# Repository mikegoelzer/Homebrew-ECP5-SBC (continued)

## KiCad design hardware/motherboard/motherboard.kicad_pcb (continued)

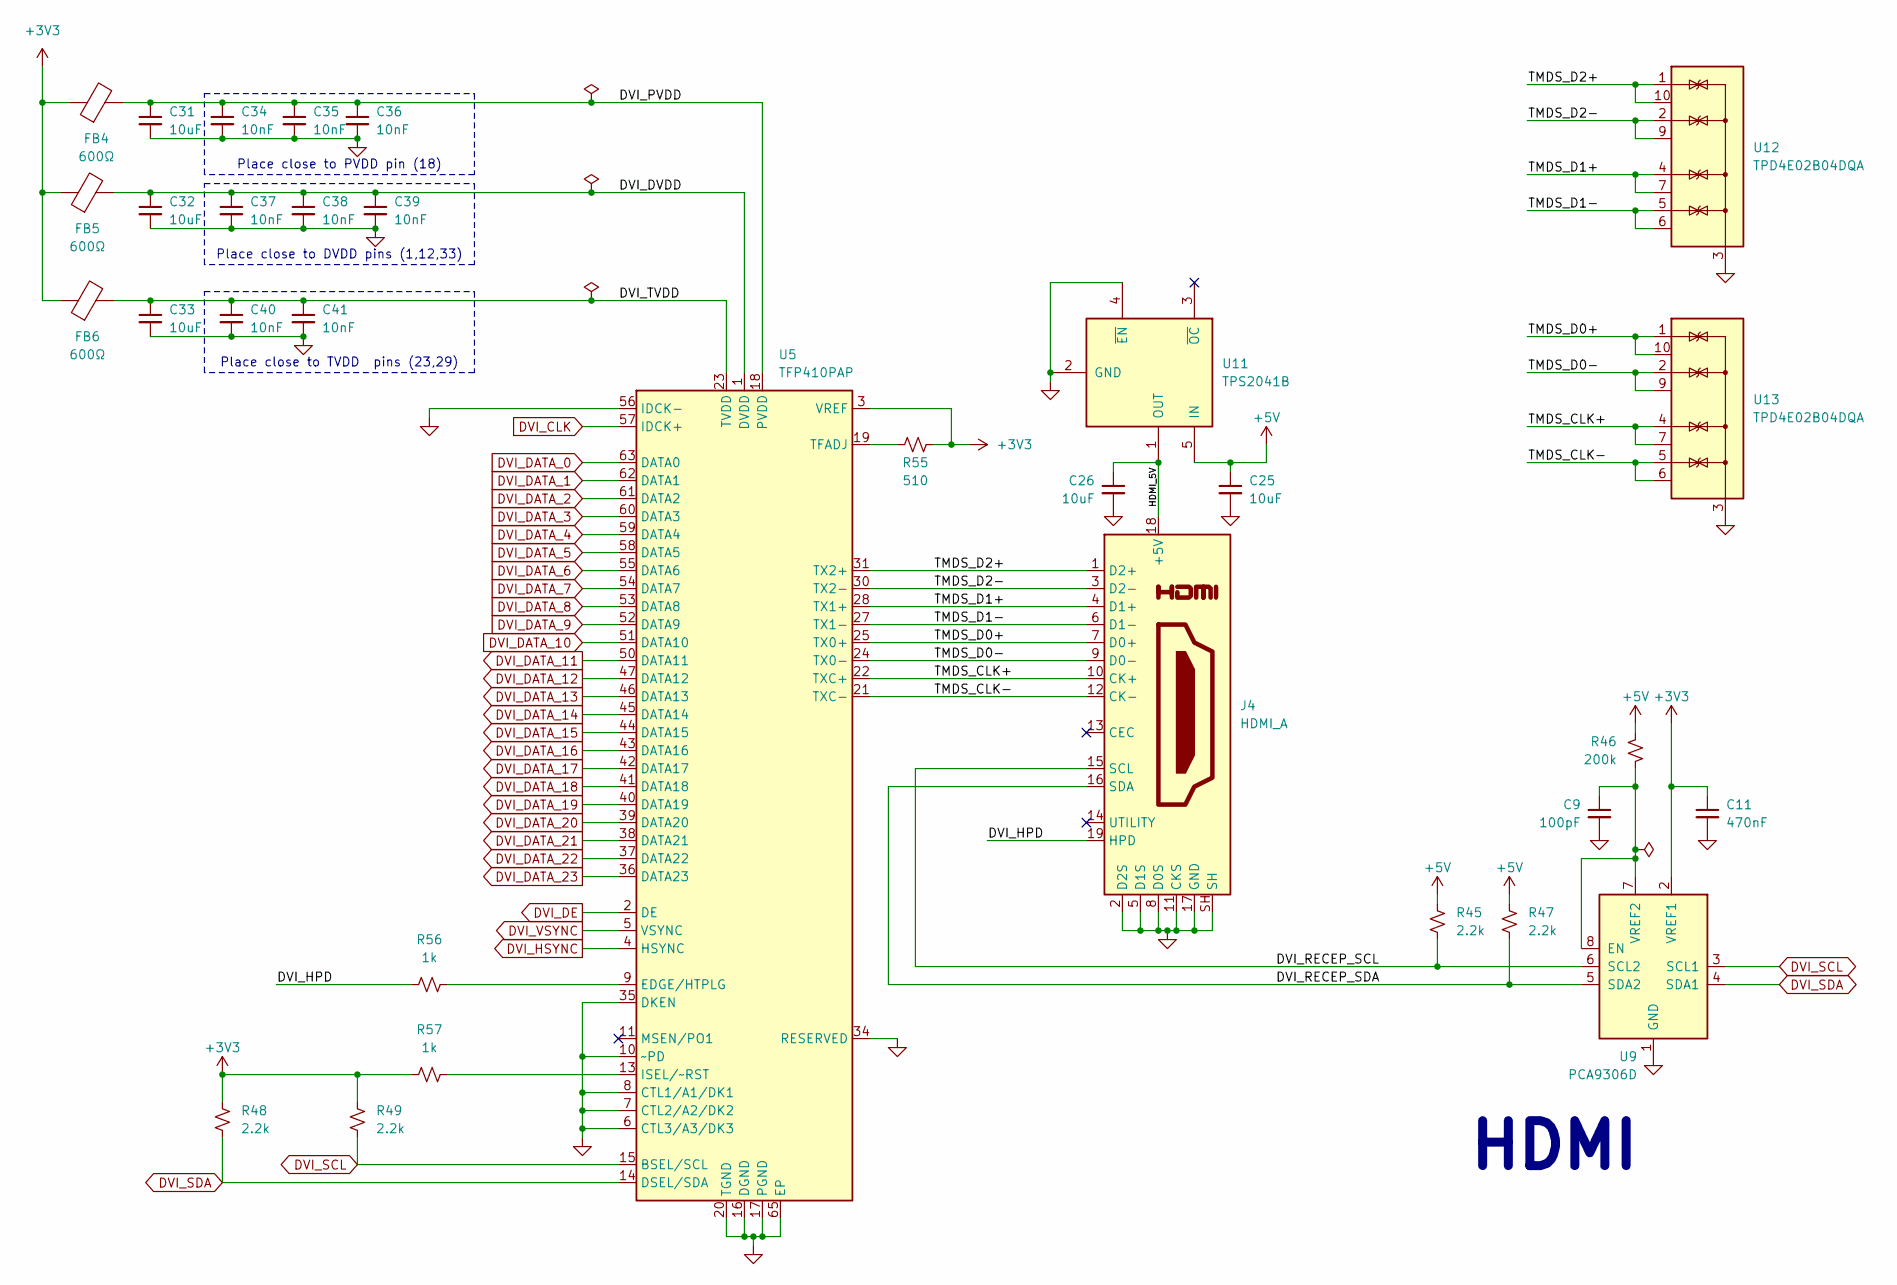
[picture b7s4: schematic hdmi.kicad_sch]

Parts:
C9: 100pF; C_0805_2012Metric_Pad1.18x1.45mm_HandSolder; MPN CC0805KRX7R9BB101
C11: 470nF; C_0805_2012Metric_Pad1.18x1.45mm_HandSolder; MPN CC0805KKX7R8BB474
C25, C26, C31, C32, C33: 10uF; C_0805_2012Metric_Pad1.18x1.45mm_HandSolder; MPN CC0805KKX5R8BB106
C34, C35, C36, C37, C38, C39, C40, C41: 10nF; C_0805_2012Metric_Pad1.18x1.45mm_HandSolder; MPN CC0805KRX7R9BB103
FB4, FB5, FB6: 600Ω; L_0603_1608Metric_Pad1.05x0.95mm_HandSolder; MPN BLM18RK601SN1D
J4: HDMI_A; HDMI_A_Molex_208658-1001_Horizontal; MPN 2086581001
R45, R47, R48, R49: 2.2k; R_0805_2012Metric_Pad1.15x1.40mm_HandSolder; MPN RC0805FR-072K2L
R46: 200k; R_0805_2012Metric_Pad1.15x1.40mm_HandSolder; MPN RC0805FR-07200KL
R55: 510; R_0805_2012Metric_Pad1.15x1.40mm_HandSolder; MPN RC0805FR-07510RL
R56, R57: 1k; R_0805_2012Metric_Pad1.15x1.40mm_HandSolder; MPN RC0805FR-071KL
U5: TFP410PAP; HTQFP-64-1EP_10x10mm_P0.5mm_EP8x8mm_Mask4.4x4.4mm_ThermalVi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; MPN TFP410PAP
U9: PCA9306D; SO-8_3.9x4.9mm_P1.27mm; MPN PCA9306D,118
U11: TPS2041B; SOT-23-5; MPN TPS2041BDBVR
U12, U13: TPD4E02B04DQA; USON-10_2.5x1.0mm_P0.5mm; MPN TPD4E02B04DQAR

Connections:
+3V3: C11.1, FB4.1, FB5.1, FB6.1, R48.1, R49.1, R55.2, R57.1, U5.3 (VREF), U9.2 (VREF1); also elsewhere on the board
+5V: C25.1, R45.1, R46.1, R47.1, U11.5 (IN); also elsewhere on the board
/HDMI/DVI_DVDD: C32.1, C37.1, C38.1, C39.1, FB5.2, U5.1 (DVDD), U5.12 (DVDD), U5.33 (DVDD)
/HDMI/DVI_HPD: J4.19 (HPD), R56.1
/HDMI/DVI_PVDD: C31.1, C34.1, C35.1, C36.1, FB4.2, U5.18 (PVDD)
/HDMI/DVI_RECEP_SCL: J4.15 (SCL), R45.2, U9.6 (SCL2)
/HDMI/DVI_RECEP_SDA: J4.16 (SDA), R47.2, U9.5 (SDA2)
/HDMI/DVI_TVDD: C33.1, C40.1, C41.1, FB6.2, U5.23 (TVDD), U5.29 (TVDD)
/HDMI/HDMI_5V: C26.1, J4.18 (+5V), U11.1 (OUT)
/HDMI/TMDS_CLK+: J4.10 (CK+), U5.22 (TXC+), U13.4 (IO3), U13.7 (NC)
/HDMI/TMDS_CLK-: J4.12 (CK-), U5.21 (TXC-), U13.5 (IO4), U13.6 (NC)
/HDMI/TMDS_D0+: J4.7 (D0+), U5.25 (TX0+), U13.1 (IO1), U13.10 (NC)
/HDMI/TMDS_D0-: J4.9 (D0-), U5.24 (TX0-), U13.2 (IO2), U13.9 (NC)
/HDMI/TMDS_D1+: J4.4 (D1+), U5.28 (TX1+), U12.4 (IO3), U12.7 (NC)
/HDMI/TMDS_D1-: J4.6 (D1-), U5.27 (TX1-), U12.5 (IO4), U12.6 (NC)
/HDMI/TMDS_D2+: J4.1 (D2+), U5.31 (TX2+), U12.1 (IO1), U12.10 (NC)
/HDMI/TMDS_D2-: J4.3 (D2-), U5.30 (TX2-), U12.2 (IO2), U12.9 (NC)
DVI_CLK: U5.57 (IDCK+); also elsewhere on the board
DVI_DATA_0: U5.63 (DATA0); also elsewhere on the board
DVI_DATA_1: U5.62 (DATA1); also elsewhere on the board
DVI_DATA_2: U5.61 (DATA2); also elsewhere on the board
DVI_DATA_3: U5.60 (DATA3); also elsewhere on the board
DVI_DATA_4: U5.59 (DATA4); also elsewhere on the board
DVI_DATA_5: U5.58 (DATA5); also elsewhere on the board
DVI_DATA_6: U5.55 (DATA6); also elsewhere on the board
DVI_DATA_7: U5.54 (DATA7); also elsewhere on the board
DVI_DATA_8: U5.53 (DATA8); also elsewhere on the board
DVI_DATA_9: U5.52 (DATA9); also elsewhere on the board
DVI_DATA_10: U5.51 (DATA10); also elsewhere on the board
DVI_DATA_11: U5.50 (DATA11); also elsewhere on the board
DVI_DATA_12: U5.47 (DATA12); also elsewhere on the board
DVI_DATA_13: U5.46 (DATA13); also elsewhere on the board
DVI_DATA_14: U5.45 (DATA14); also elsewhere on the board
DVI_DATA_15: U5.44 (DATA15); also elsewhere on the board
DVI_DATA_16: U5.43 (DATA16); also elsewhere on the board
DVI_DATA_17: U5.42 (DATA17); also elsewhere on the board
DVI_DATA_18: U5.41 (DATA18); also elsewhere on the board
DVI_DATA_19: U5.40 (DATA19); also elsewhere on the board
DVI_DATA_20: U5.39 (DATA20); also elsewhere on the board
DVI_DATA_21: U5.38 (DATA21); also elsewhere on the board
DVI_DATA_22: U5.37 (DATA22); also elsewhere on the board
DVI_DATA_23: U5.36 (DATA23); also elsewhere on the board
DVI_DE: U5.2 (DE); also elsewhere on the board
DVI_HSYNC: U5.4 (HSYNC); also elsewhere on the board
DVI_SCL: R49.2, U5.15 (BSEL/SCL), U9.3 (SCL1); also elsewhere on the board
DVI_SDA: R48.2, U5.14 (DSEL/SDA), U9.4 (SDA1); also elsewhere on the board
DVI_VSYNC: U5.5 (VSYNC); also elsewhere on the board
GND: C9.2, C11.2, C25.2, C26.2, C31.2, C32.2, C33.2, C34.2, C35.2, C36.2, C37.2, C38.2, C39.2, C40.2, C41.2, J4.2 (D2S), J4.5 (D1S), J4.8 (D0S), J4.11 (CKS), J4.17 (GND), J4.SH, U5.6 (CTL3/A3/DK3), U5.7 (CTL2/A2/DK2), U5.8 (CTL1/A1/DK1), U5.10 (~PD), U5.16 (DGND), U5.17 (PGND), U5.20 (TGND), U5.26 (TGND), U5.32 (TGND), U5.34 (RESERVED), U5.35 (DKEN), U5.48 (DGND), U5.56 (IDCK-), U5.64 (DGND), U5.65 (EP), U9.1 (GND), U11.2 (GND), U11.4 (~EN), U12.3 (G), U12.8 (G), U13.3 (G), U13.8 (G); also elsewhere on the board
unnamed: R56.2, U5.9 (EDGE/HTPLG)
unnamed: R57.2, U5.13 (ISEL/~RST)
unnamed: R55.1, U5.19 (TFADJ)
unnamed: C9.1, R46.2, U9.7 (VREF2), U9.8 (EN)

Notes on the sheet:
HDMI
Place close to DVDD pins (1,12,33)
Place close to TVDD pins (23,29)
Place close to PVDD pin (18)

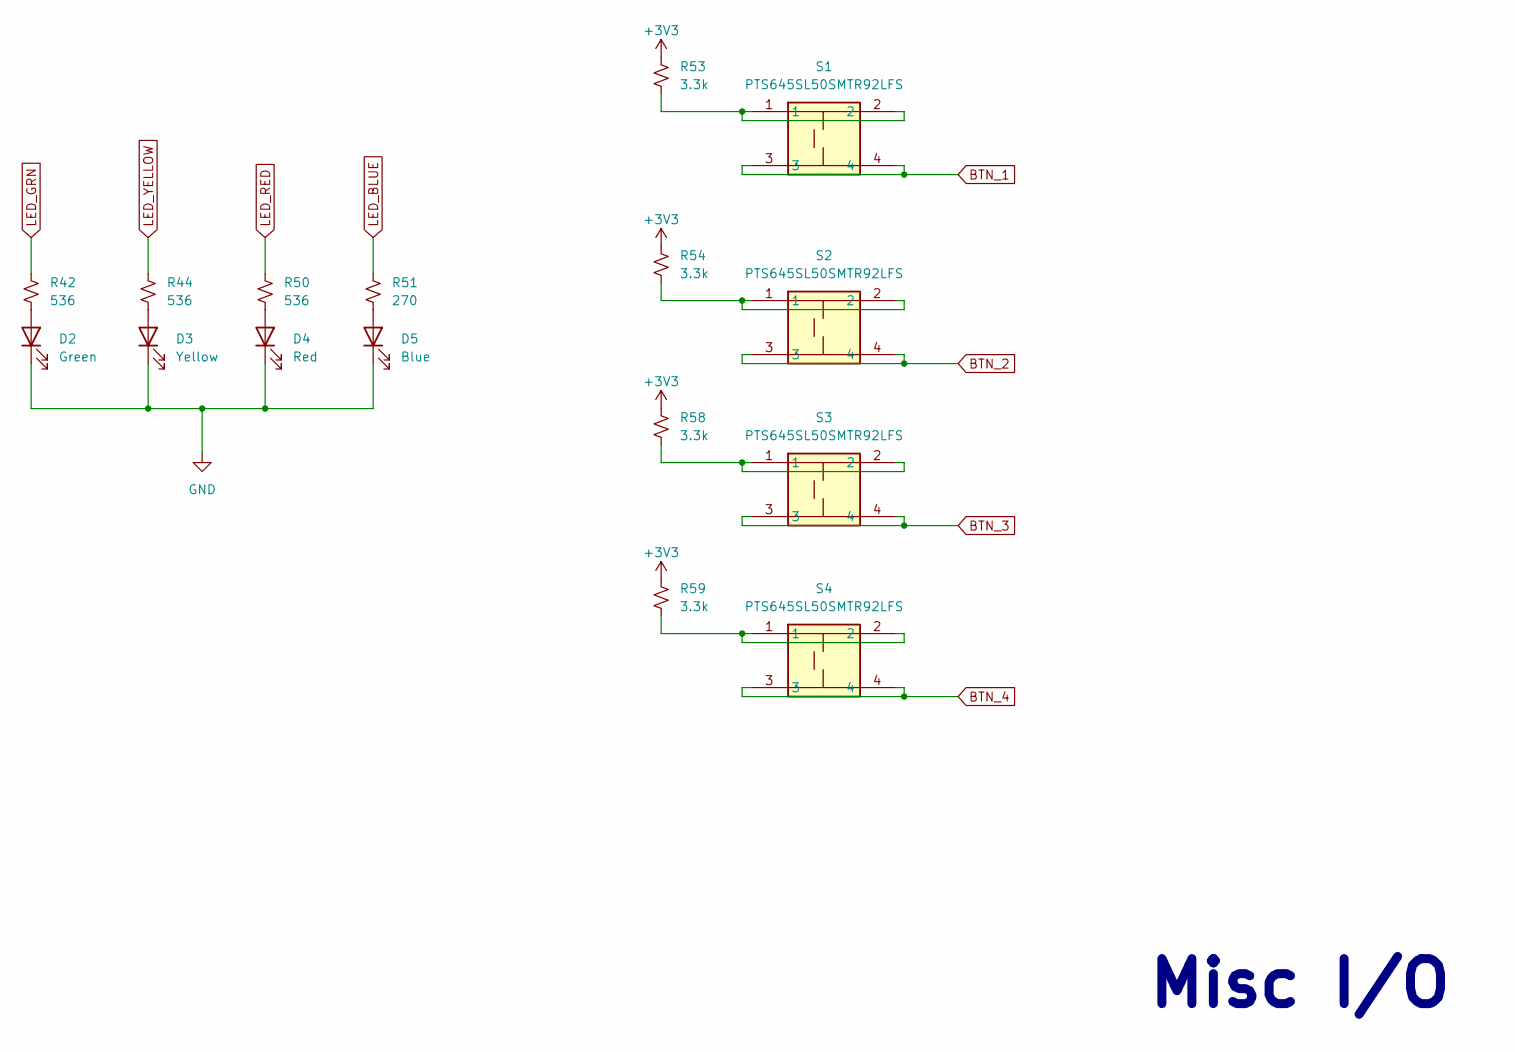
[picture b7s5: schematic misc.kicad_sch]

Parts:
D2: Green; Wurth_150080xS7500_0805; MPN 150080VS75000
D3: Yellow; Wurth_150080xS7500_0805; MPN 150080YS75000
D4: Red; Wurth_150080xS7500_0805; MPN 150080SS75000
D5: Blue; Wurth_150080xS7500_0805; MPN 150080BS75000
R42, R44, R50: 536; R_0805_2012Metric_Pad1.15x1.40mm; MPN RC0805FR-07536RL
R51: 270; R_0805_2012Metric_Pad1.15x1.40mm; MPN RC0805FR-07270RL
R53, R54, R58, R59: 3.3k; R_0805_2012Metric_Pad1.15x1.40mm; MPN RC0805FR-073K3L
S1, S2, S3, S4: PTS645SL50SMTR92LFS; PTS645SMT; Mouser Part Number 611-PTS645SL50SMTR92

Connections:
+3V3: R53.1, R54.1, R58.1, R59.1; also elsewhere on the board
BTN_1: S1.3, S1.4; also elsewhere on the board
BTN_2: S2.3, S2.4; also elsewhere on the board
BTN_3: S3.3, S3.4; also elsewhere on the board
BTN_4: S4.3, S4.4; also elsewhere on the board
GND: D2.1 (K), D3.1 (K), D4.1 (K), D5.1 (K); also elsewhere on the board
LED_BLUE: R51.1; also elsewhere on the board
LED_GRN: R42.1; also elsewhere on the board
LED_RED: R50.1; also elsewhere on the board
LED_YELLOW: R44.1; also elsewhere on the board
unnamed: D2.2 (A), R42.2
unnamed: D3.2 (A), R44.2
unnamed: D4.2 (A), R50.2
unnamed: D5.2 (A), R51.2
unnamed: R53.2, S1.1, S1.2
unnamed: R54.2, S2.1, S2.2
unnamed: R58.2, S3.1, S3.2
unnamed: R59.2, S4.1, S4.2

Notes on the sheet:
Misc I/O

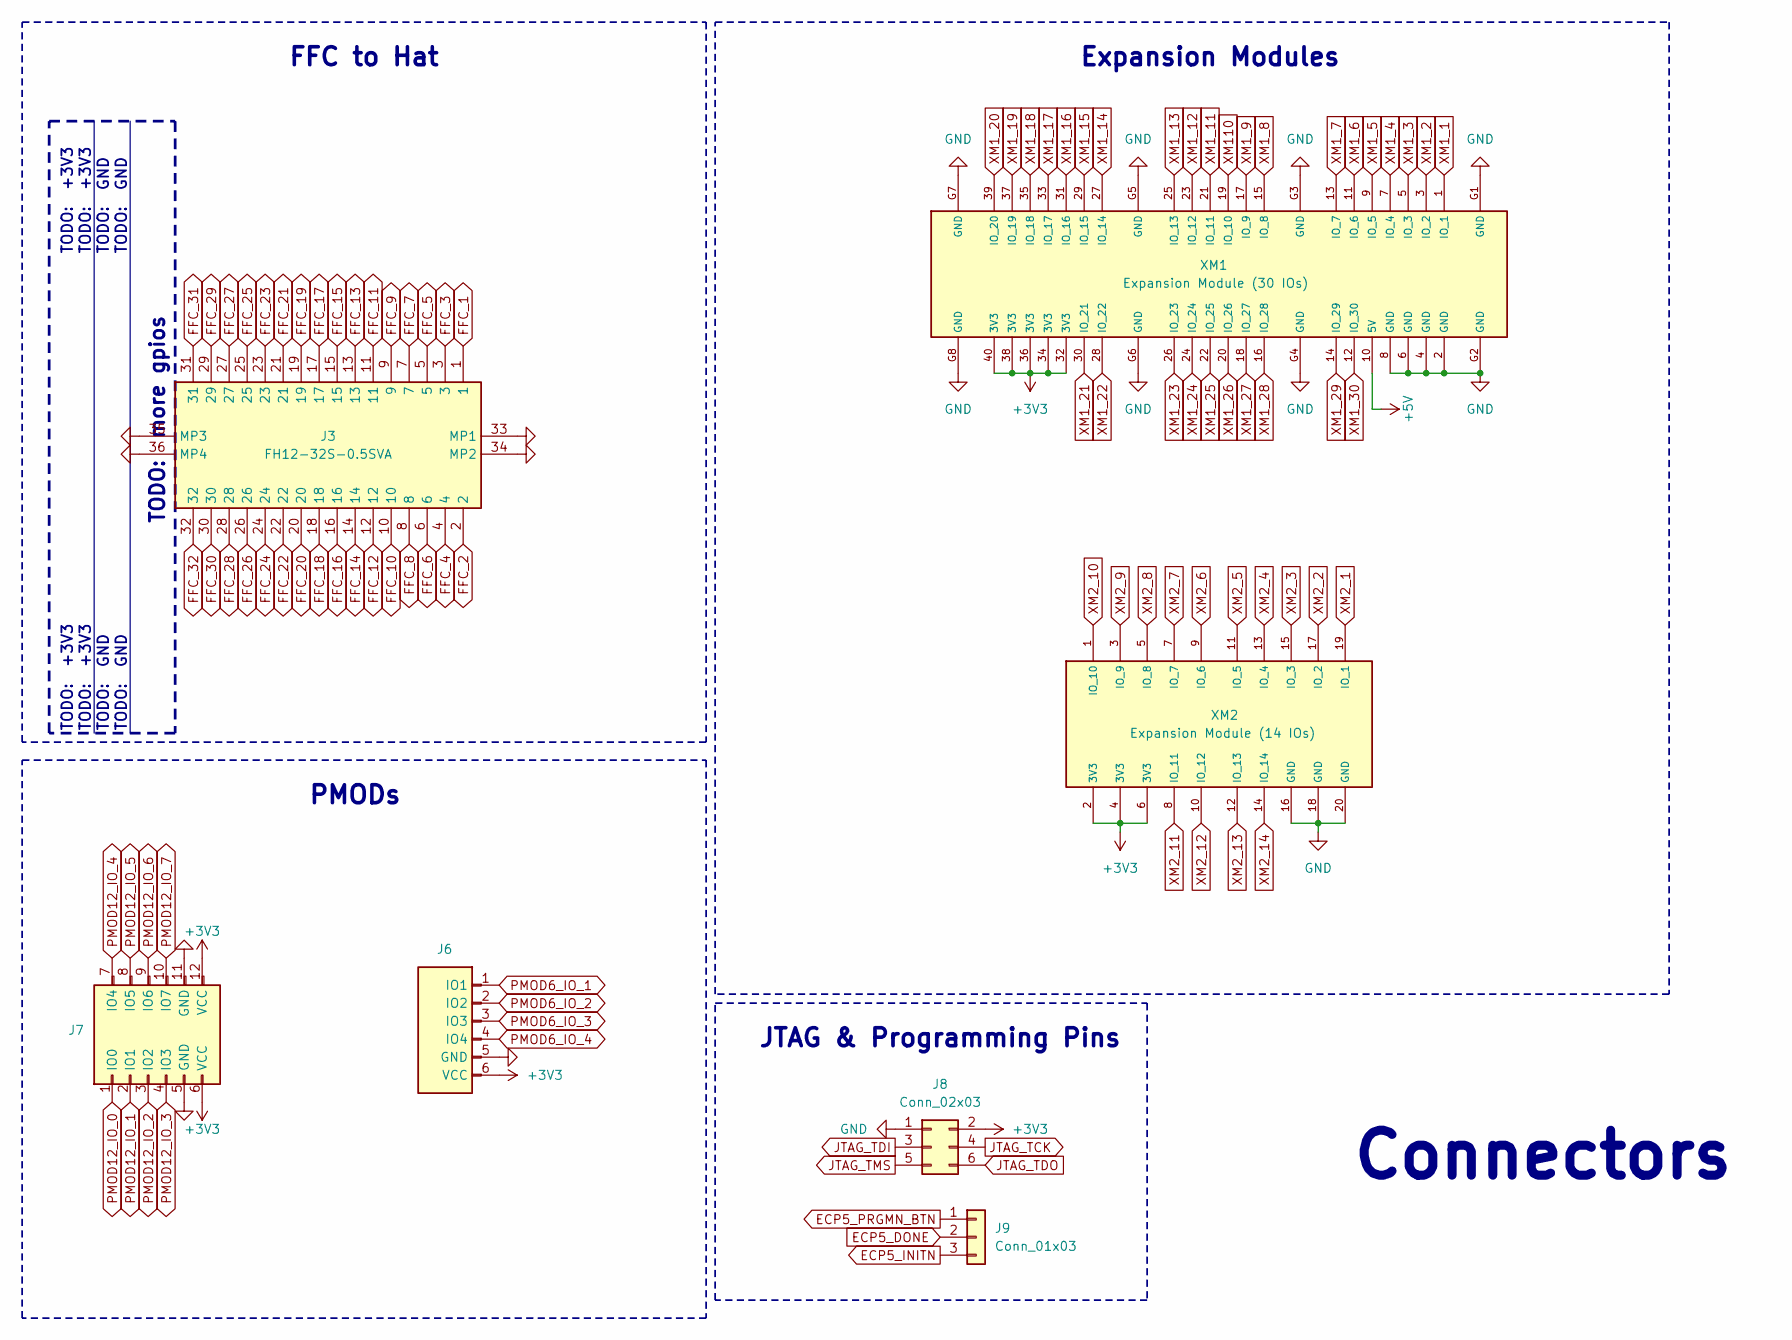
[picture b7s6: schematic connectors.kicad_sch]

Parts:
J3: FH12-32S-0.5SVA; FH1232S05SVA54; Mouser Part Number 798-FH1232S0.5SVA54
J6: PMOD_6; MPN PH1RB-06-UA
J7: PMOD_12; MPN PH2RA-12-UA
J8: Conn_02x03; CONN_PH2-06-UA_ADM; MPN PH2-06-UA
J9: Conn_01x03; PinHeader_1x03_P2.54mm_Vertical; MPN PH1-03-UA
XM1: Expansion Module (30 IOs); XM30
XM2: Expansion Module (14 IOs); XM14

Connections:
+3V3: J6.6 (VCC), J7.6 (VCC), J7.12 (VCC), J8.2 (+12V), XM1.32 (3V3), XM1.34 (3V3), XM1.36 (3V3), XM1.38 (3V3), XM1.40 (3V3), XM2.2 (3V3), XM2.4 (3V3), XM2.6 (3V3); also elsewhere on the board
+5V: XM1.10 (5V); also elsewhere on the board
ECP5_DONE: J9.2; also elsewhere on the board
ECP5_INITN: J9.3; also elsewhere on the board
ECP5_PRGMN_BTN: J9.1; also elsewhere on the board
FFC_1: J3.1; also elsewhere on the board
FFC_2: J3.2; also elsewhere on the board
FFC_3: J3.3; also elsewhere on the board
FFC_4: J3.4; also elsewhere on the board
FFC_5: J3.5; also elsewhere on the board
FFC_6: J3.6; also elsewhere on the board
FFC_7: J3.7; also elsewhere on the board
FFC_8: J3.8; also elsewhere on the board
FFC_9: J3.9; also elsewhere on the board
FFC_10: J3.10; also elsewhere on the board
FFC_11: J3.11; also elsewhere on the board
FFC_12: J3.12; also elsewhere on the board
FFC_13: J3.13; also elsewhere on the board
FFC_14: J3.14; also elsewhere on the board
FFC_15: J3.15; also elsewhere on the board
FFC_16: J3.16; also elsewhere on the board
FFC_17: J3.17; also elsewhere on the board
FFC_18: J3.18; also elsewhere on the board
FFC_19: J3.19; also elsewhere on the board
FFC_20: J3.20; also elsewhere on the board
FFC_21: J3.21; also elsewhere on the board
FFC_22: J3.22; also elsewhere on the board
FFC_23: J3.23; also elsewhere on the board
FFC_24: J3.24; also elsewhere on the board
FFC_25: J3.25; also elsewhere on the board
FFC_26: J3.26; also elsewhere on the board
FFC_27: J3.27; also elsewhere on the board
FFC_28: J3.28; also elsewhere on the board
FFC_29: J3.29; also elsewhere on the board
FFC_30: J3.30; also elsewhere on the board
FFC_31: J3.31; also elsewhere on the board
FFC_32: J3.32; also elsewhere on the board
GND: J3.33 (MP1), J3.34 (MP2), J3.35 (MP3), J3.36 (MP4), J6.5 (GND), J7.5 (GND), J7.11 (GND), J8.1 (+12V), XM1.2 (GND), XM1.4 (GND), XM1.6 (GND), XM1.8 (GND), XM1.G1 (GND), XM1.G2 (GND), XM1.G3 (GND), XM1.G4 (GND), XM1.G5 (GND), XM1.G6 (GND), XM1.G7 (GND), XM1.G8 (GND), XM2.16 (GND), XM2.18 (GND), XM2.20 (GND); also elsewhere on the board
JTAG_TCK: J8.4 (GND); also elsewhere on the board
JTAG_TDI: J8.3 (GND); also elsewhere on the board
JTAG_TDO: J8.6 (GND); also elsewhere on the board
JTAG_TMS: J8.5 (GND); also elsewhere on the board
PMOD6_IO_1: J6.1 (IO1); also elsewhere on the board
PMOD6_IO_2: J6.2 (IO2); also elsewhere on the board
PMOD6_IO_3: J6.3 (IO3); also elsewhere on the board
PMOD6_IO_4: J6.4 (IO4); also elsewhere on the board
PMOD12_IO_0: J7.1 (IO0); also elsewhere on the board
PMOD12_IO_1: J7.2 (IO1); also elsewhere on the board
PMOD12_IO_2: J7.3 (IO2); also elsewhere on the board
PMOD12_IO_3: J7.4 (IO3); also elsewhere on the board
PMOD12_IO_4: J7.7 (IO4); also elsewhere on the board
PMOD12_IO_5: J7.8 (IO5); also elsewhere on the board
PMOD12_IO_6: J7.9 (IO6); also elsewhere on the board
PMOD12_IO_7: J7.10 (IO7); also elsewhere on the board
XM1_1: XM1.1 (IO_1); also elsewhere on the board
XM1_2: XM1.3 (IO_2); also elsewhere on the board
XM1_3: XM1.5 (IO_3); also elsewhere on the board
XM1_4: XM1.7 (IO_4); also elsewhere on the board
XM1_5: XM1.9 (IO_5); also elsewhere on the board
XM1_6: XM1.11 (IO_6); also elsewhere on the board
XM1_7: XM1.13 (IO_7); also elsewhere on the board
XM1_8: XM1.15 (IO_8); also elsewhere on the board
XM1_9: XM1.17 (IO_9); also elsewhere on the board
XM1_11: XM1.21 (IO_11); also elsewhere on the board
XM1_12: XM1.23 (IO_12); also elsewhere on the board
XM1_13: XM1.25 (IO_13); also elsewhere on the board
XM1_14: XM1.27 (IO_14); also elsewhere on the board
XM1_15: XM1.29 (IO_15); also elsewhere on the board
XM1_16: XM1.31 (IO_16); also elsewhere on the board
XM1_17: XM1.33 (IO_17); also elsewhere on the board
XM1_18: XM1.35 (IO_18); also elsewhere on the board
XM1_19: XM1.37 (IO_19); also elsewhere on the board
XM1_20: XM1.39 (IO_20); also elsewhere on the board
XM1_21: XM1.30 (IO_21); also elsewhere on the board
XM1_22: XM1.28 (IO_22); also elsewhere on the board
XM1_23: XM1.26 (IO_23); also elsewhere on the board
XM1_24: XM1.24 (IO_24); also elsewhere on the board
XM1_25: XM1.22 (IO_25); also elsewhere on the board
XM1_26: XM1.20 (IO_26); also elsewhere on the board
XM1_27: XM1.18 (IO_27); also elsewhere on the board
XM1_28: XM1.16 (IO_28); also elsewhere on the board
XM1_29: XM1.14 (IO_29); also elsewhere on the board
XM1_30: XM1.12 (IO_30); also elsewhere on the board
XM2_1: XM2.19 (IO_1); also elsewhere on the board
XM2_2: XM2.17 (IO_2); also elsewhere on the board
XM2_3: XM2.15 (IO_3); also elsewhere on the board
XM2_4: XM2.13 (IO_4); also elsewhere on the board
XM2_5: XM2.11 (IO_5); also elsewhere on the board
XM2_6: XM2.9 (IO_6); also elsewhere on the board
XM2_7: XM2.7 (IO_7); also elsewhere on the board
XM2_8: XM2.5 (IO_8); also elsewhere on the board
XM2_9: XM2.3 (IO_9); also elsewhere on the board
XM2_10: XM2.1 (IO_10); also elsewhere on the board
XM2_11: XM2.8 (IO_11); also elsewhere on the board
XM2_12: XM2.10 (IO_12); also elsewhere on the board
XM2_13: XM2.12 (IO_13); also elsewhere on the board
XM2_14: XM2.14 (IO_14); also elsewhere on the board
XM110: XM1.19 (IO_10); also elsewhere on the board

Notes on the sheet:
FFC to Hat
TODO: GND
TODO: +3V3
Expansion Modules
PMODs
JTAG & Programming Pins
TODO: more gpios
Connectors

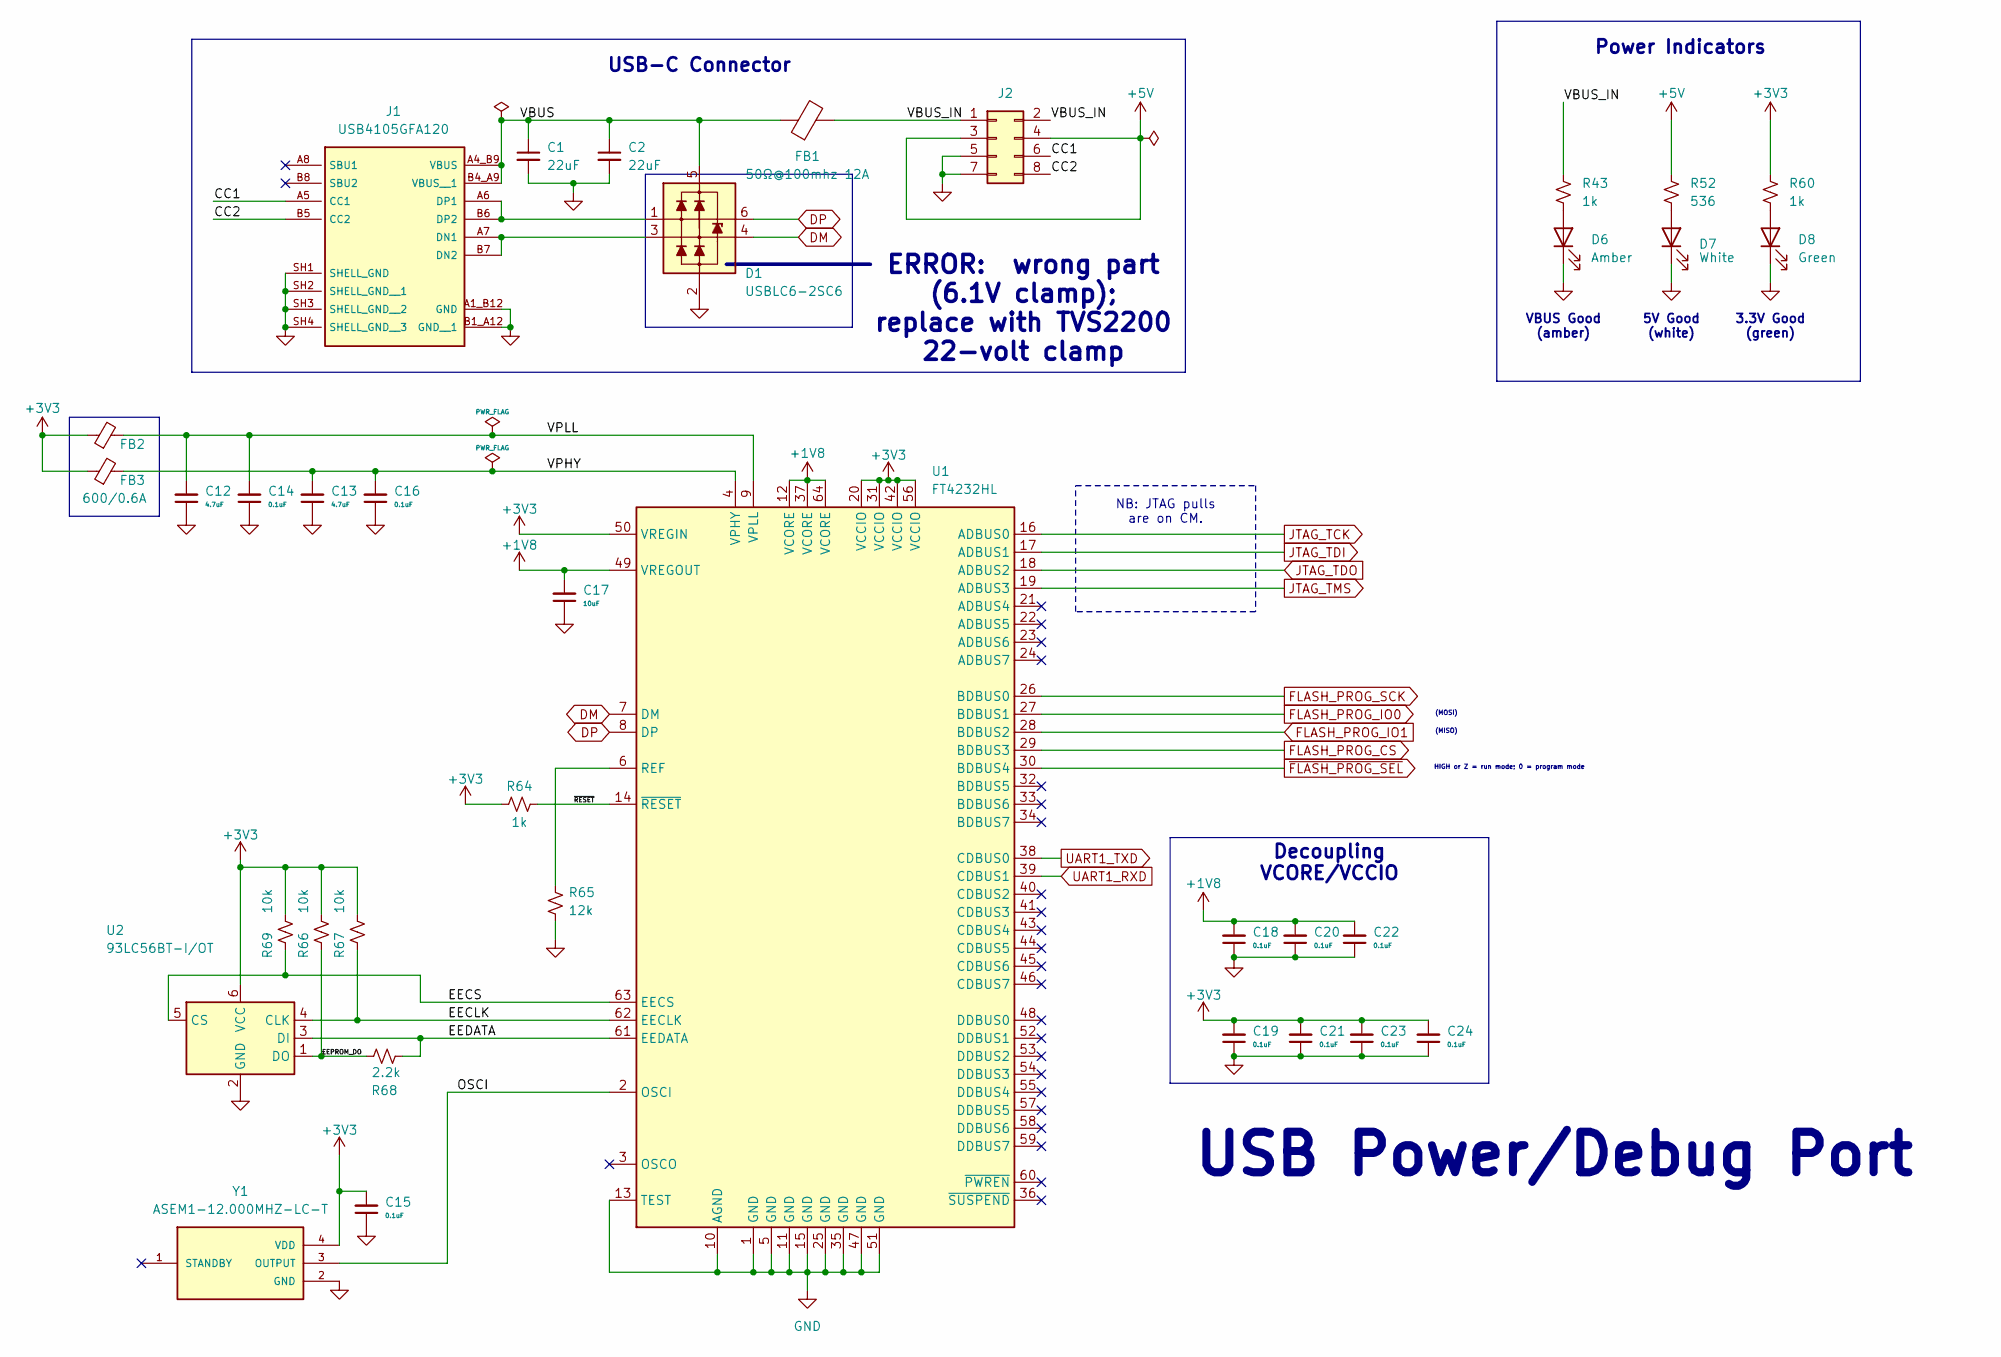
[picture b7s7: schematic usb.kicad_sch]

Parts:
C1, C2: 22uF; C_0805_2012Metric_Pad1.18x1.45mm_HandSolder; MPN C2012X5R1V226M125AC
C12, C13: 4.7uF; C_0805_2012Metric_Pad1.18x1.45mm_HandSolder; MPN CC0805KKX5R8BB475
C14, C16, C18, C19, C20, C21, C22, C23, C24: 0.1uF; C_0805_2012Metric_Pad1.18x1.45mm_HandSolder; MPN CC0805KRX7R9BB104
C15: 0.1uF; C_0805_2012Metric_Pad1.18x1.45mm_HandSolder
C17: 10uF; C_0805_2012Metric_Pad1.18x1.45mm_HandSolder; MPN CC0805KKX5R8BB106
D1: USBLC6-2SC6; SOT-23-6; MPN USBLC6-2SC6
D6: Amber; Wurth_150080xS7500_0805; MPN 150080AS75000
D7: White; QBLP631_White_LED_0805; MPN QBLP631-IW
D8: Green; Wurth_150080xS7500_0805; MPN 150080VS75000
FB1: 50Ω@100mhz 12A; L_1206_3216Metric_Pad1.42x1.75mm_HandSolder; MPN BLM31SN500SZ1L
FB2, FB3: 600/0.6A; L_0805_2012Metric_Pad1.15x1.40mm_HandSolder; MPN BLM21AG601SN1D
J1: USB4105GFA120; GCT_USB4105GFA120; MPN USB4105-GF-A-120
J2: Conn_02x04_Odd_Even; PinSocket_2x04_P2.54mm_Vertical; MPN RS2-08-G
R43, R60: 1k; R_0805_2012Metric_Pad1.15x1.40mm; MPN RC0805FR-071KL
R52: 536; R_0805_2012Metric_Pad1.15x1.40mm; MPN RC0805FR-07536RL
R64: 1k; R_0805_2012Metric_Pad1.15x1.40mm_HandSolder; MPN RC0805FR-071KL
R65: 12k; R_0805_2012Metric_Pad1.15x1.40mm_HandSolder; MPN RC0805FR-0712KL
R66, R67, R69: 10k; R_0805_2012Metric_Pad1.15x1.40mm_HandSolder; MPN RC0805FR-0710KL
R68: 2.2k; R_0805_2012Metric_Pad1.15x1.40mm_HandSolder; MPN RC0805FR-072K2L
U1: FT4232HL; LQFP-64_10x10mm_P0.5mm; MPN FT4232HL-REEL
U2: 93LC56BT-I/OT; SOT-23-6; MPN 93LC56BT-I/OT
Y1: ASEM1-12.000MHZ-LC-T; XTAL_ASEM1-12.000MHZ-LC-T; MPN ASEM1-12.000MHZ-LC-T

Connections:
+1V8: C17.2, C18.2, C20.2, C22.2, U1.12 (VCORE), U1.37 (VCORE), U1.49 (VREGOUT), U1.64 (VCORE)
+3V3: C15.2, C19.2, C21.2, C23.2, C24.2, FB2.1, FB3.1, R60.1, R64.1, R66.1, R67.1, R69.1, U1.20 (VCCIO), U1.31 (VCCIO), U1.42 (VCCIO), U1.50 (VREGIN), U1.56 (VCCIO), U2.6 (VCC), Y1.4 (VDD); also elsewhere on the board
+5V: J2.3, J2.4, R52.1; also elsewhere on the board
/USB-C Power & Debug Port/CC1: J1.A5 (CC1), J2.6
/USB-C Power & Debug Port/CC2: J1.B5 (CC2), J2.8
/USB-C Power & Debug Port/EECLK: R67.2, U1.62 (EECLK), U2.4 (CLK)
/USB-C Power & Debug Port/EECS: R69.2, U1.63 (EECS), U2.5 (CS)
/USB-C Power & Debug Port/EEDATA: R68.2, U1.61 (EEDATA), U2.3 (DI)
/USB-C Power & Debug Port/EEPROM_DO: R66.2, R68.1, U2.1 (DO)
/USB-C Power & Debug Port/OSCI: U1.2 (OSCI), Y1.3 (OUTPUT)
/USB-C Power & Debug Port/VBUS: C1.1, C2.1, D1.5 (VP), FB1.1, J1.A4_B9 (VBUS), J1.B4_A9 (VBUS__1)
/USB-C Power & Debug Port/VBUS_IN: FB1.2, J2.1, J2.2, R43.1
/USB-C Power & Debug Port/VPHY: C13.2, C16.2, FB3.2, U1.4 (VPHY)
/USB-C Power & Debug Port/VPLL: C12.2, C14.2, FB2.2, U1.9 (VPLL)
/USB-C Power & Debug Port/~RESET: R64.2, U1.14 (~RESET)
DM: D1.4 (L2), U1.7 (DM)
DP: D1.6 (L1), U1.8 (DP)
FLASH_PROG_CS: U1.29 (BDBUS3); also elsewhere on the board
FLASH_PROG_IO0: U1.27 (BDBUS1); also elsewhere on the board
FLASH_PROG_IO1: U1.28 (BDBUS2); also elsewhere on the board
FLASH_PROG_SCK: U1.26 (BDBUS0); also elsewhere on the board
GND: C1.2, C2.2, C12.1, C13.1, C14.1, C15.1, C16.1, C17.1, C18.1, C19.1, C20.1, C21.1, C22.1, C23.1, C24.1, D1.2 (VN), D6.1 (K), D7.2 (K), D8.1 (K), J1.A1_B12 (GND), J1.B1_A12 (GND__1), J1.SH1 (SHELL_GND), J1.SH2 (SHELL_GND__1), J1.SH3 (SHELL_GND__2), J1.SH4 (SHELL_GND__3), J2.5, J2.7, R65.2, U1.1 (GND), U1.5 (GND), U1.10 (AGND), U1.11 (GND), U1.13 (TEST), U1.15 (GND), U1.25 (GND), U1.35 (GND), U1.47 (GND), U1.51 (GND), U2.2 (GND), Y1.2 (GND); also elsewhere on the board
JTAG_TCK: U1.16 (ADBUS0); also elsewhere on the board
JTAG_TDI: U1.17 (ADBUS1); also elsewhere on the board
JTAG_TDO: U1.18 (ADBUS2); also elsewhere on the board
JTAG_TMS: U1.19 (ADBUS3); also elsewhere on the board
unnamed: D6.2 (A), R43.2
unnamed: D7.1 (A), R52.2
unnamed: D8.2 (A), R60.2
unnamed: D1.3 (L2), J1.A7 (DN1), J1.B7 (DN2)
unnamed: D1.1 (L1), J1.A6 (DP1), J1.B6 (DP2)
unnamed: R65.1, U1.6 (REF)
UART1_RXD: U1.39 (CDBUS1); also elsewhere on the board
UART1_TXD: U1.38 (CDBUS0); also elsewhere on the board
~FLASH_PROG_SEL: U1.30 (BDBUS4); also elsewhere on the board

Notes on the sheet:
USB-C Connector
(MISO)
3.3V Good (green)
Power Indicators
ERROR: wrong part (6.1V clamp); replace with TVS2200 22-volt clamp
USB Power/Debug Port
(MOSI)
Decoupling VCORE/VCCIO
HIGH or Z = run mode; 0 = program mode
VBUS Good (amber)
5V Good (white)
NB: JTAG pulls are on CM.

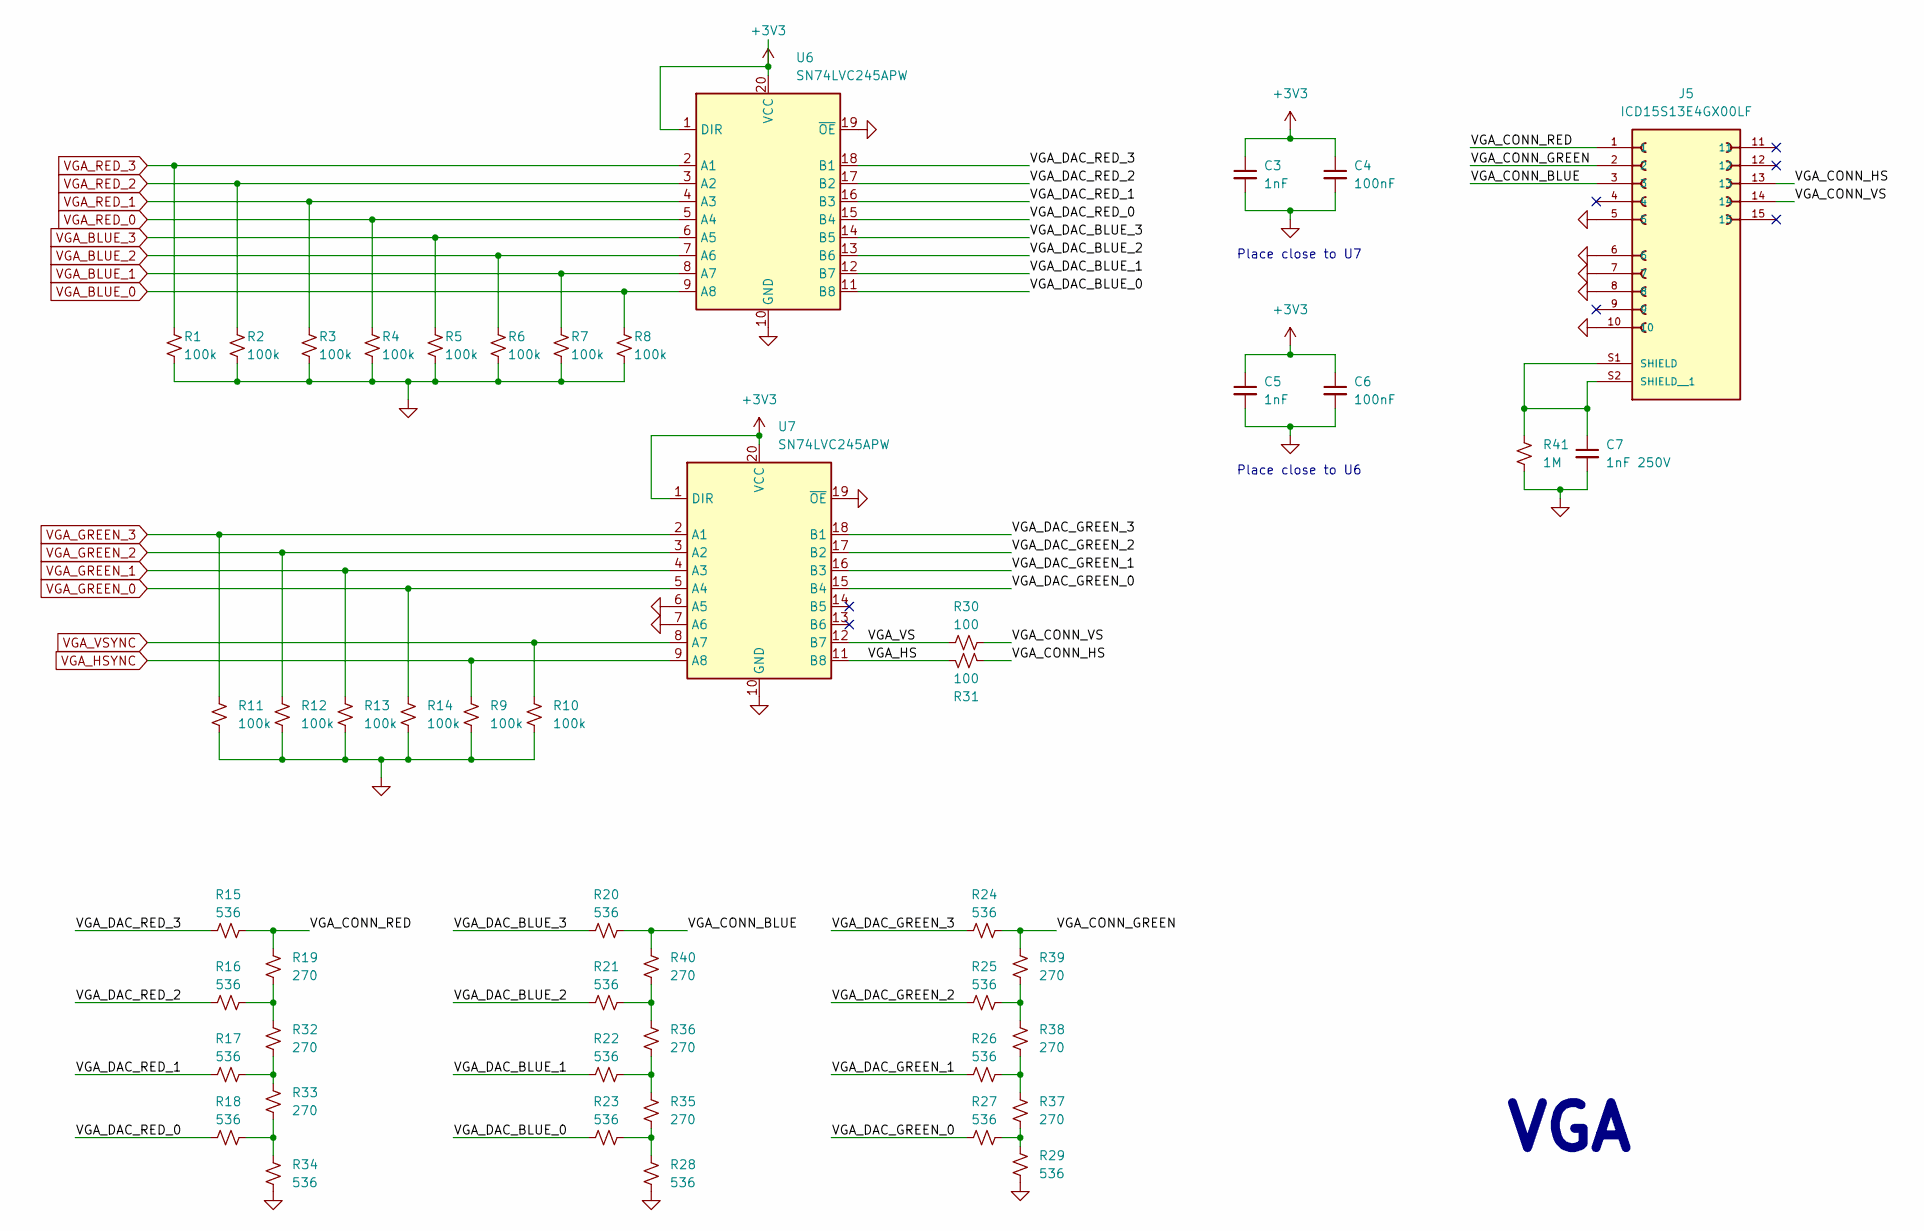
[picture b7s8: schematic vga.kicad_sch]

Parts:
C3, C5: 1nF; C_0805_2012Metric_Pad1.18x1.45mm_HandSolder; MPN CC0805KRX7R9BB102
C4, C6: 100nF; C_0805_2012Metric_Pad1.18x1.45mm_HandSolder; MPN CC0805KRX7R9BB104
C7: 1nF 250V; C_0805_2012Metric_Pad1.18x1.45mm_HandSolder; MPN CL21B102KECSFNC
J5: ICD15S13E4GX00LF; AMPHENOL_ICD15S13E4GX00LF; MPN ICD15S13E4GX00LF
R1, R2, R3, R4, R5, R6, R7, R8, R9, R10, R11, R12, R13, R14: 100k; R_0805_2012Metric_Pad1.15x1.40mm; MPN RC0805FR-07100KL
R15, R16, R17, R18, R20, R21, R22, R23, R24, R25, R26, R27, R28, R29, R34: 536; R_0805_2012Metric_Pad1.15x1.40mm; MPN RC0805FR-07536RL
R19, R32, R33, R35, R36, R37, R38, R39, R40: 270; R_0805_2012Metric_Pad1.15x1.40mm; MPN RC0805FR-07270RL
R30, R31: 100; R_0805_2012Metric_Pad1.15x1.40mm; MPN RC0805FR-07100RL
R41: 1M; R_0805_2012Metric_Pad1.15x1.40mm; MPN RC0805FR-071ML
U6, U7: SN74LVC245APW; TSSOP-20_4.4x6.5mm_P0.65mm

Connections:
+3V3: C3.1, C4.1, C5.1, C6.1, U6.1 (DIR), U6.20 (VCC), U7.1 (DIR), U7.20 (VCC); also elsewhere on the board
/VGA/VGA_CONN_BLUE: J5.3, R20.2, R40.1
/VGA/VGA_CONN_GREEN: J5.2, R24.2, R39.1
/VGA/VGA_CONN_HS: J5.13, R31.2
/VGA/VGA_CONN_RED: J5.1, R15.2, R19.1
/VGA/VGA_CONN_VS: J5.14, R30.1
/VGA/VGA_DAC_BLUE_0: R23.1, U6.11 (B8)
/VGA/VGA_DAC_BLUE_1: R22.1, U6.12 (B7)
/VGA/VGA_DAC_BLUE_2: R21.1, U6.13 (B6)
/VGA/VGA_DAC_BLUE_3: R20.1, U6.14 (B5)
/VGA/VGA_DAC_GREEN_0: R27.1, U7.15 (B4)
/VGA/VGA_DAC_GREEN_1: R26.1, U7.16 (B3)
/VGA/VGA_DAC_GREEN_2: R25.1, U7.17 (B2)
/VGA/VGA_DAC_GREEN_3: R24.1, U7.18 (B1)
/VGA/VGA_DAC_RED_0: R18.1, U6.15 (B4)
/VGA/VGA_DAC_RED_1: R17.1, U6.16 (B3)
/VGA/VGA_DAC_RED_2: R16.1, U6.17 (B2)
/VGA/VGA_DAC_RED_3: R15.1, U6.18 (B1)
/VGA/VGA_HS: R31.1, U7.11 (B8)
/VGA/VGA_VS: R30.2, U7.12 (B7)
GND: C3.2, C4.2, C5.2, C6.2, C7.2, J5.5, J5.6, J5.7, J5.8, J5.10, R1.2, R2.2, R3.2, R4.2, R5.2, R6.2, R7.2, R8.2, R9.2, R10.2, R11.2, R12.2, R13.2, R14.2, R28.2, R29.2, R34.2, R41.2, U6.10 (GND), U6.19 (~OE), U7.6 (A5), U7.7 (A6), U7.10 (GND), U7.19 (~OE); also elsewhere on the board
unnamed: C7.1, J5.S1 (SHIELD), J5.S2 (SHIELD__1), R41.1
unnamed: R16.2, R19.2, R32.1
unnamed: R17.2, R32.2, R33.1
unnamed: R18.2, R33.2, R34.1
unnamed: R21.2, R36.1, R40.2
unnamed: R22.2, R35.1, R36.2
unnamed: R23.2, R28.1, R35.2
unnamed: R25.2, R38.1, R39.2
unnamed: R26.2, R37.1, R38.2
unnamed: R27.2, R29.1, R37.2
VGA_BLUE_0: R8.1, U6.9 (A8); also elsewhere on the board
VGA_BLUE_1: R7.1, U6.8 (A7); also elsewhere on the board
VGA_BLUE_2: R6.1, U6.7 (A6); also elsewhere on the board
VGA_BLUE_3: R5.1, U6.6 (A5); also elsewhere on the board
VGA_GREEN_0: R14.1, U7.5 (A4); also elsewhere on the board
VGA_GREEN_1: R13.1, U7.4 (A3); also elsewhere on the board
VGA_GREEN_2: R12.1, U7.3 (A2); also elsewhere on the board
VGA_GREEN_3: R11.1, U7.2 (A1); also elsewhere on the board
VGA_HSYNC: R9.1, U7.9 (A8); also elsewhere on the board
VGA_RED_0: R4.1, U6.5 (A4); also elsewhere on the board
VGA_RED_1: R3.1, U6.4 (A3); also elsewhere on the board
VGA_RED_2: R2.1, U6.3 (A2); also elsewhere on the board
VGA_RED_3: R1.1, U6.2 (A1); also elsewhere on the board
VGA_VSYNC: R10.1, U7.8 (A7); also elsewhere on the board

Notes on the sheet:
Place close to U6
Place close to U7
VGA
